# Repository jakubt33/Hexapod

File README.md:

Hexapod
=======

0b00 - Start communication in manual mode
0b01 - Start communication in auto mode
0b10 - Next bite
0b11 - End of message

Manual:
0b00|x x x x x x
0b10|L L L L L L 
0b10|L T T T T T
0b11|S S S S S P

Auto:
0b01|C C C C C c
0b11|c S S S S P

x - wchich leg is to be activated (1-6)
L - lift position
T - turn position
S - speed
P - power on(1)/power off(0)
c - command
C - Curve

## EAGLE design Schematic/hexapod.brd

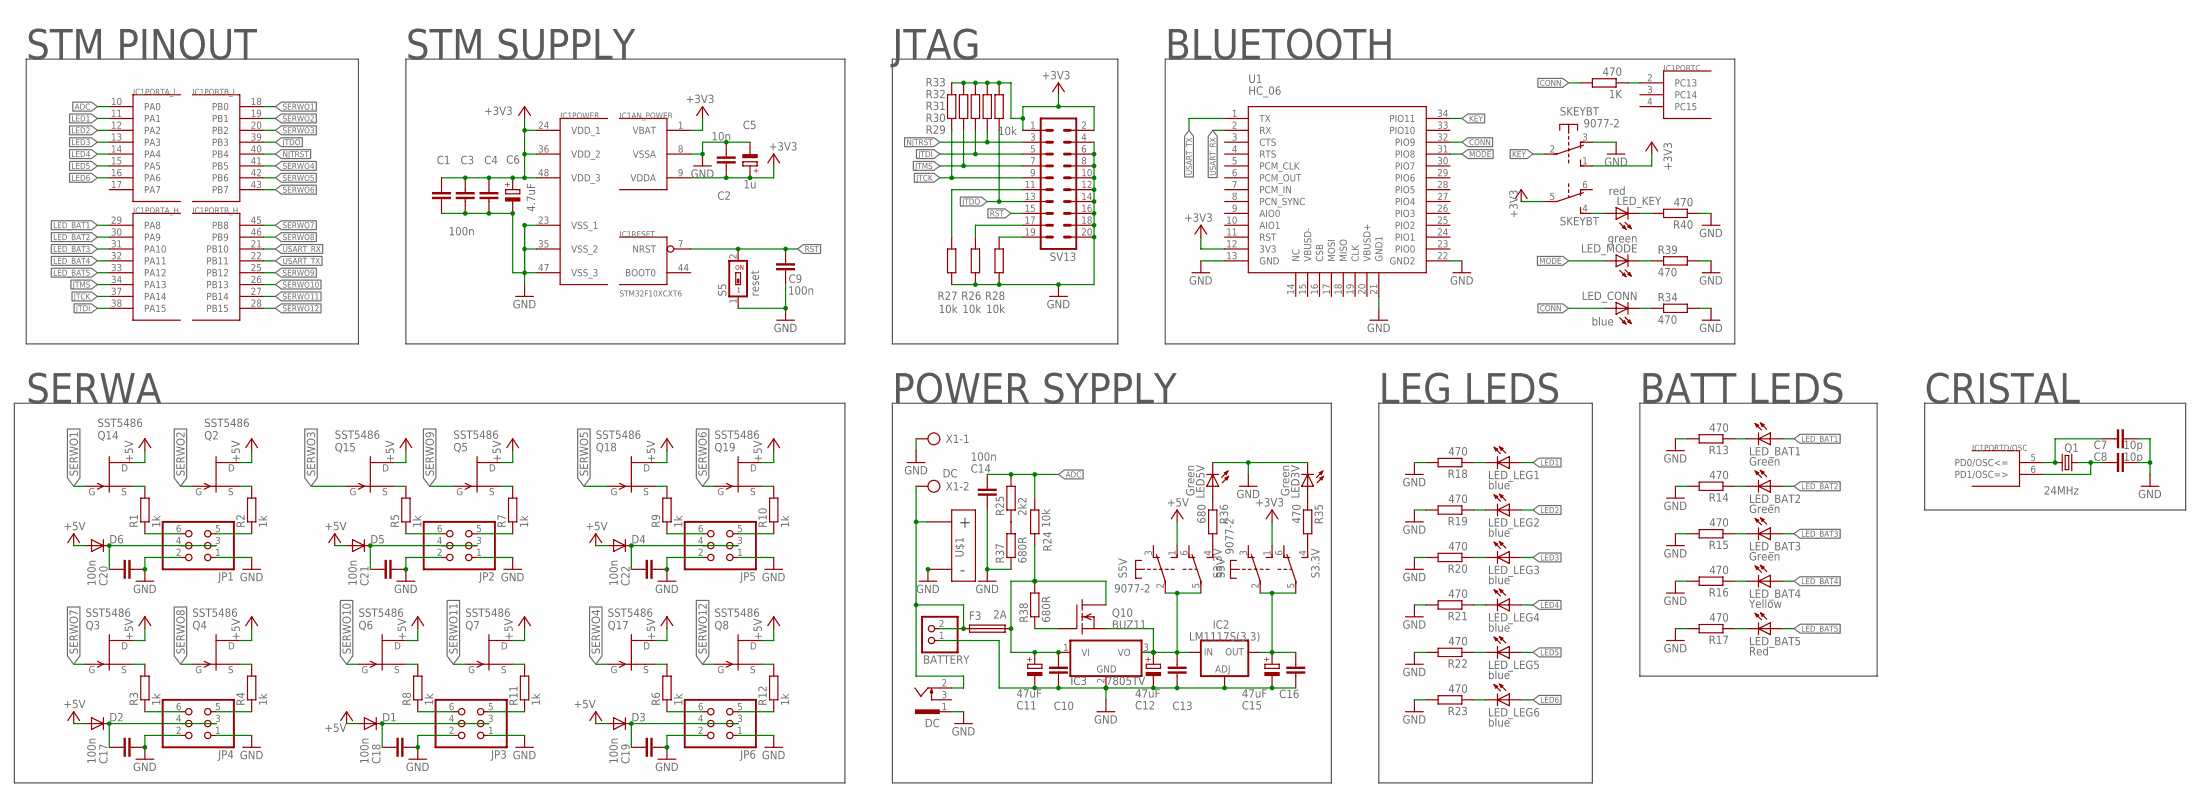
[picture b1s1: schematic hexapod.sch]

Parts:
1K: 470; M0805
BATTERY: PINHD-1X2; 1X02
C1, C3, C4, C9, C10, C13, C14, C16, C17, C18, C19, C20, C21, C22: 100n; C0805K
C2: 10n; C0805K
C5: 1u; E2,5-5
C6: 4.7uF; E2,5-5
C7, C8: 10p; C0805K
C11, C12, C15: 47uF; E2,5-5
D1, D2, D3, D4, D5, D6: DIODE-DO-214AC; DO-214AC
DC: 733980-62
F3: 2A; SH22,5
IC1: STM32F10XCXT6; TQFP48
IC2: LM1117S(3.3); SOT223
IC3: 7805TV; TO220V
JP1, JP2, JP3, JP4, JP5, JP6: PINHD-2X3; 2X03
LED3V, LED5V: Green; CHIP-LED0805
LED_BAT1, LED_BAT2, LED_BAT3: Green; CHIP-LED0805
LED_BAT4: Yellow; CHIP-LED0805
LED_BAT5: Red; CHIP-LED0805
LED_CONN: blue; CHIP-LED0805
LED_KEY: red; CHIP-LED0805
LED_LEG1, LED_LEG2, LED_LEG3, LED_LEG4, LED_LEG5, LED_LEG6: blue; CHIP-LED0805
LED_MODE: green; CHIP-LED0805
Q1: 24MHz; SM49
Q2, Q3, Q4, Q5, Q6, Q7, Q8, Q14, Q15, Q17, Q18, Q19: SST5486; SOT23
Q10: BUZ11; TO220
R1, R2, R3, R4, R5, R6, R7, R8, R9, R10, R11, R12: 1k; M0805
R13, R14, R15, R16, R17, R18, R19, R20, R21, R22, R23, R34, R35, R39, R40: 470; M0805
R24, R26, R27, R28, R29, R30, R31, R32, R33: 10k; M0805
R25: 2k2; M0805
R36: 680; M0805
R37, R38: 680R; M0805
S3.3V, S5V: 9077-2
S5: reset; SMS-001
SKEYBT: 9077-2
SV13: ML20
U1: HC_06; BLUETOOTH_SMD
U$1: DEANS.MALE; DEANSM
X1: DC; AK500/2

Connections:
+3V3: C1.1, C2.1, C3.1, C4.1, C5.+, C6.+, IC1.1 (VBAT), IC1.9 (VDDA), IC1.24 (VDD_1), IC1.36 (VDD_2), IC1.48 (VDD_3), R29.2, R30.2, R31.2, R32.2, R33.2, S3.3V.1 (S), SKEYBT.1 (S), SKEYBT.5, SV13.1, SV13.2, U1.12 (3V3)
+5V: D1.A, D2.A, D3.A, D4.A, D5.A, D6.A, Q2.1 (D), Q3.1 (D), Q4.1 (D), Q5.1 (D), Q6.1 (D), Q7.1 (D), Q8.1 (D), Q14.1 (D), Q15.1 (D), Q17.1 (D), Q18.1 (D), Q19.1 (D), S5V.1 (S)
ADC: C14.1, IC1.10 (PA0), R24.1, R25.2
CONN: 1K.2, LED_CONN.A, U1.32 (PIO9)
GND: BATTERY.1, C1.2, C2.2, C3.2, C4.2, C5.-, C6.-, C7.2, C8.2, C9.1, C10.2, C11.-, C12.-, C13.2, C14.2, C15.-, C16.2, C17.2, C18.2, C19.2, C20.2, C21.2, C22.2, DC.1, IC1.8 (VSSA), IC1.23 (VSS_1), IC1.35 (VSS_2), IC1.47 (VSS_3), IC2.1 (ADJ), IC3.2 (GND), JP1.1, JP1.2, JP2.1, JP2.2, JP3.1, JP3.2, JP4.1, JP4.2, JP5.1, JP5.2, JP6.1, JP6.2, LED3V.C, LED5V.C, R13.2, R14.2, R15.2, R16.2, R17.2, R18.2, R19.2, R20.2, R21.2, R22.2, R23.2, R26.1, R27.1, R28.1, R34.2, R37.1, R39.2, R40.1, S5.1, SKEYBT.3 (O), SV13.4, SV13.6, SV13.8, SV13.10, SV13.12, SV13.14, SV13.16, SV13.18, SV13.20, U1.13 (GND), U1.21 (GND1), U1.22 (GND2), U$1.P$NEG, X1.1
JTCK: IC1.37 (PA14), R29.1, SV13.9
JTDI: IC1.38 (PA15), R31.1, SV13.5
JTDO: IC1.39 (PB3), R33.1, SV13.13
JTMS: IC1.34 (PA13), R30.1, SV13.7
KEY: SKEYBT.2, U1.34 (PIO11)
LED1: IC1.11 (PA1), LED_LEG1.A
LED2: IC1.12 (PA2), LED_LEG2.A
LED3: IC1.13 (PA3), LED_LEG3.A
LED4: IC1.14 (PA4), LED_LEG4.A
LED5: IC1.15 (PA5), LED_LEG5.A
LED6: IC1.16 (PA6), LED_LEG6.A
LED_BAT1: IC1.29 (PA8), LED_BAT1.A
LED_BAT2: IC1.30 (PA9), LED_BAT2.A
LED_BAT3: IC1.31 (PA10), LED_BAT3.A
LED_BAT4: IC1.32 (PA11), LED_BAT4.A
LED_BAT5: IC1.33 (PA12), LED_BAT5.A
MODE: LED_MODE.A, U1.31 (PIO8)
unnamed: C7.1, IC1.5 (PD0/OSC<=), Q1.2
unnamed: C8.1, IC1.6 (PD1/OSC=>), Q1.1
unnamed: 1K.1, IC1.2 (PC13)
unnamed: Q14.2 (S), R1.2
unnamed: JP5.5, R10.1
unnamed: Q2.2 (S), R2.2
unnamed: JP3.5, R11.1
unnamed: JP5.6, R9.1
unnamed: JP3.6, R8.1
unnamed: R25.1, R37.2
unnamed: JP6.5, R12.1
unnamed: Q15.2 (S), R5.2
unnamed: JP2.5, R7.1
unnamed: Q18.2 (S), R9.2
unnamed: JP2.6, R5.1
unnamed: JP6.6, R6.1
unnamed: JP1.6, R1.1
unnamed: JP4.6, R3.1
unnamed: JP4.5, R4.1
unnamed: Q19.2 (S), R10.2
unnamed: JP1.5, R2.1
unnamed: R36.2, S5V.4 (S)
unnamed: C10.1, C11.+, F3.2, IC3.1 (VI), Q10.2 (D), R24.2, R38.2
unnamed: Q10.1 (G), R38.1
unnamed: LED_MODE.C, R39.1
unnamed: LED_KEY.A, SKEYBT.4 (S)
unnamed: LED_KEY.C, R40.2
unnamed: LED_BAT1.C, R13.1
unnamed: LED_LEG1.C, R18.1
unnamed: LED_BAT2.C, R14.1
unnamed: LED_LEG2.C, R19.1
unnamed: LED_BAT3.C, R15.1
unnamed: LED_LEG3.C, R20.1
unnamed: LED_BAT4.C, R16.1
unnamed: LED_LEG4.C, R21.1
unnamed: LED_BAT5.C, R17.1
unnamed: LED_LEG5.C, R22.1
unnamed: LED_LEG6.C, R23.1
unnamed: C18.1, D1.C, JP3.3, JP3.4
unnamed: LED_CONN.C, R34.1
unnamed: C15.+, C16.1, IC2.4 (OUT), S3.3V.2, S3.3V.5
unnamed: C12.+, C13.1, IC2.3 (IN), IC3.3 (VO), Q10.3 (S), S5V.2, S5V.5
unnamed: Q17.2 (S), R6.2
unnamed: R27.2, SV13.11
unnamed: Q3.2 (S), R3.2
unnamed: R35.2, S3.3V.4 (S)
unnamed: R26.2, SV13.17
unnamed: R28.2, SV13.19
unnamed: LED3V.A, R35.1
unnamed: C17.1, D2.C, JP4.3, JP4.4
unnamed: LED5V.A, R36.1
unnamed: BATTERY.2, DC.2, F3.1, U$1.P$POS, X1.2
unnamed: Q4.2 (S), R4.2
unnamed: Q5.2 (S), R7.2
unnamed: Q6.2 (S), R8.2
unnamed: Q7.2 (S), R11.2
unnamed: Q8.2 (S), R12.2
unnamed: C19.1, D3.C, JP6.3, JP6.4
unnamed: C22.1, D4.C, JP5.3, JP5.4
unnamed: C21.1, D5.C, JP2.3, JP2.4
unnamed: C20.1, D6.C, JP1.3, JP1.4
NJTRST: IC1.40 (PB4), R32.1, SV13.3
RST: C9.2, IC1.7 (NRST), S5.2, SV13.15
SERWO1: IC1.18 (PB0), Q14.3 (G)
SERWO2: IC1.19 (PB1), Q2.3 (G)
SERWO3: IC1.20 (PB2), Q15.3 (G)
SERWO4: IC1.41 (PB5), Q17.3 (G)
SERWO5: IC1.42 (PB6), Q18.3 (G)
SERWO6: IC1.43 (PB7), Q19.3 (G)
SERWO7: IC1.45 (PB8), Q3.3 (G)
SERWO8: IC1.46 (PB9), Q4.3 (G)
SERWO9: IC1.25 (PB12), Q5.3 (G)
SERWO10: IC1.26 (PB13), Q6.3 (G)
SERWO11: IC1.27 (PB14), Q7.3 (G)
SERWO12: IC1.28 (PB15), Q8.3 (G)
USART_RX: IC1.21 (PB10), U1.2 (RX)
USART_TX: IC1.22 (PB11), U1.1 (TX)

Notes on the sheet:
SERWA
BATT LEDS
LEG LEDS
POWER SYPPLY
JTAG
STM SUPPLY
CRISTAL
STM PINOUT
BLUETOOTH

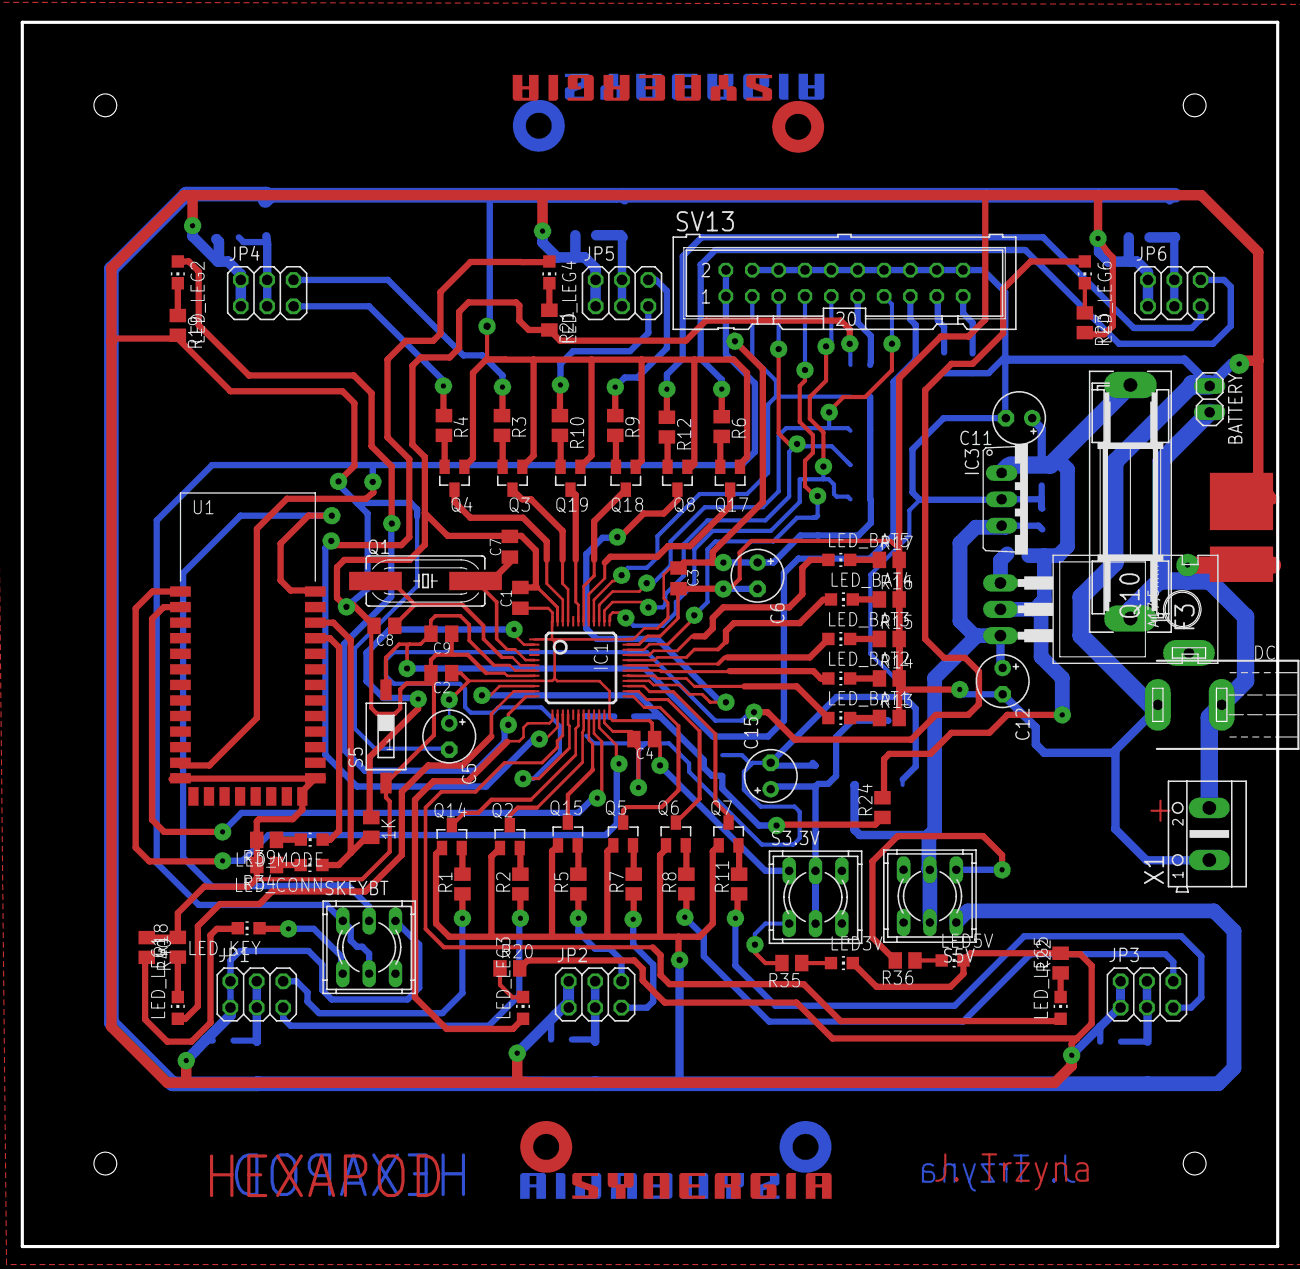
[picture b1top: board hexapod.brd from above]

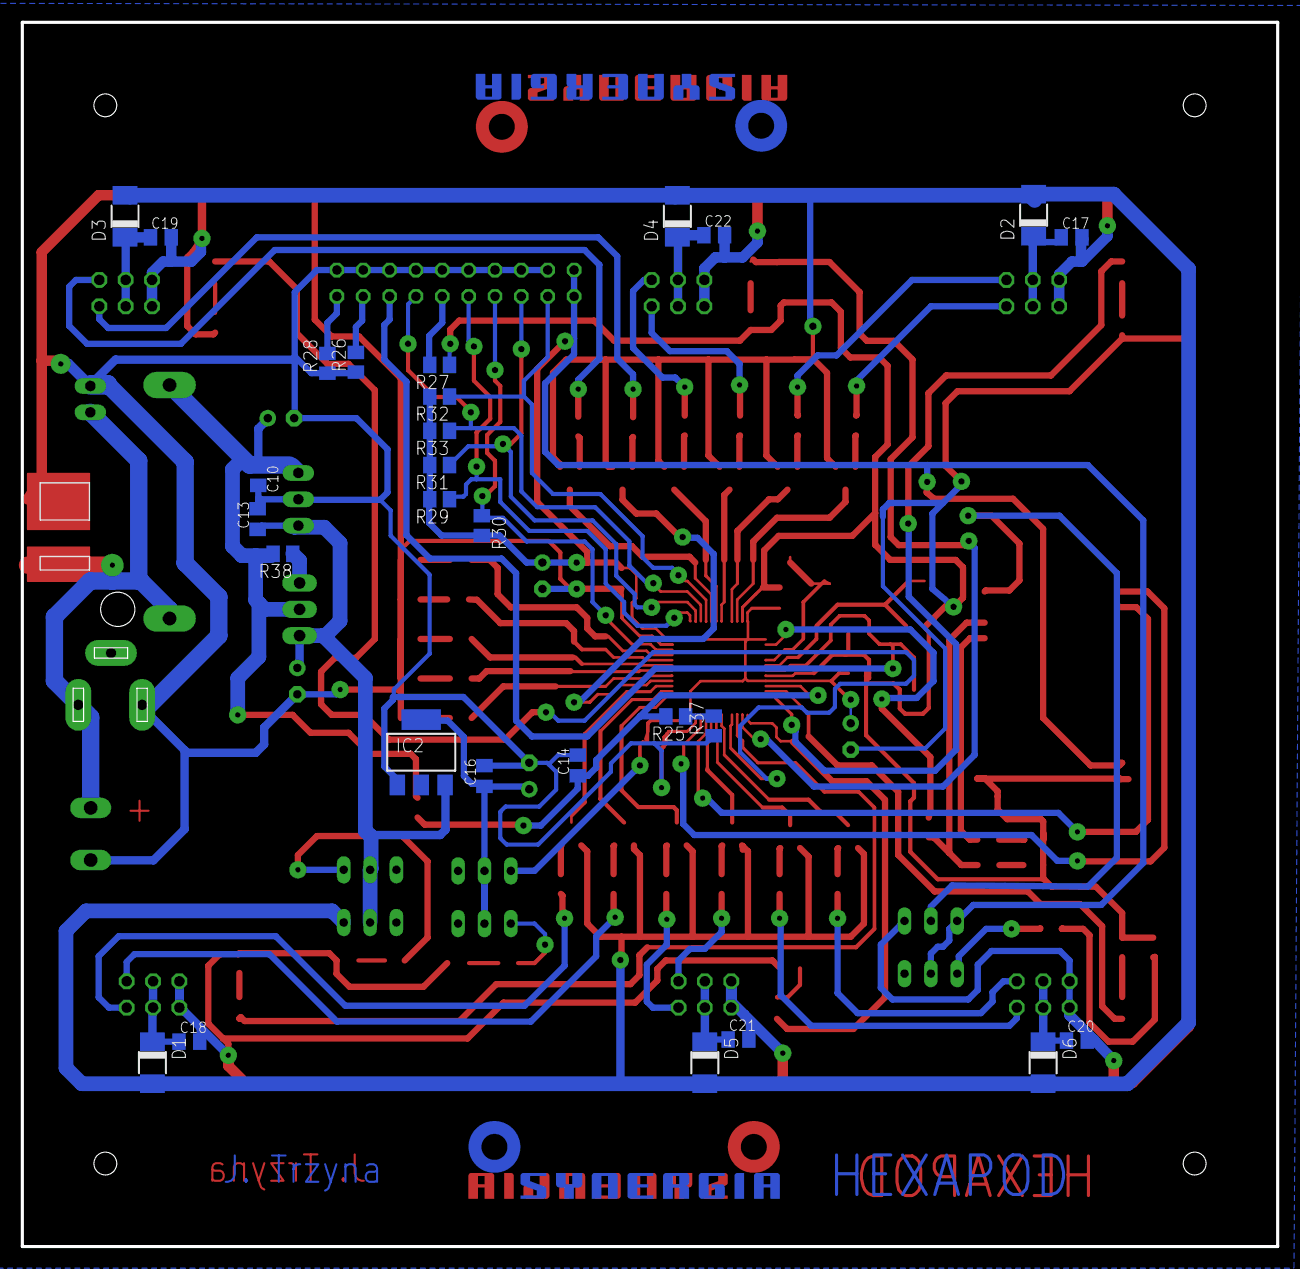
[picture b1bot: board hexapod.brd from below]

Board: 2 copper layers, 121.0 x 118.0 mm, 123 parts (30 on the bottom side), 99 nets.

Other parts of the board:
U$2, U$3, U$4, U$5: SYNERGIA_30MM

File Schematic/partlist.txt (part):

Partlist

Exported from hexapod.brd at 2014-07-22 17:38:38

EAGLE Version 6.4.0 Copyright (c) 1988-2013 CadSoft

Assembly variant: 

Part     Value          Package       Library             Position (inch)       Orientation

BATTERY                 1X02          pinhead             (5.87 1.42)           R90
C1       100n           C0805K        rcl                 (2.52 2.8)            R90
C2       10n            C0805K        rcl                 (2.22 2.53)           R180
C3       100n           C0805K        rcl                 (3.12 2.89)           R270
C4       100n           C0805K        rcl                 (2.99 2.28)           R180
C5       1u             E2,5-5        rcl                 (2.25 2.29)           R270
C6       4.7uF          E2,5-5        rcl                 (3.42 2.9)            R270
C7       10p            C0805K        rcl                 (2.48 3.01)           R90
C8       10p            C0805K        rcl                 (1.98 2.71)           R180
C9       100n           C0805K        rcl                 (2.2 2.71)            R0
C10      100n           C0805K        rcl                 (4.05 2.87)           MR90
C11      47uF           E2,5-5        rcl                 (4.25 2.78)           R270
C12      47uF           E2,5-5        rcl                 (4.25 2.52)           R270
C13      100n           C0805K        rcl                 (4 2.54)              MR270
C14      100n           C0805K        rcl                 (4.16 2.02)           R90
C15      47uF           E2,5-5        rcl                 (3.47 2.14)           R90
C16      100n           C0805K        rcl                 (3.64 2.14)           MR90
DC                      733980-62     con-conrad          (5.79 2.28)           R90
F3       2A             SH22,5        fuse                (4.57 2.39)           R90
IC1      STM32F10XCXT6  TQFP48        stm32               (2.75 2.55)           R270
IC2      LM1117S(3.3)   SOT223        v-reg               (3.92 2.23)           MR0
IC4      LM1117S(5)     SOT223        v-reg               (3.78 2.7)            MR180
LED3V    Green          CHIP-LED0805  led                 (3.74 1.43)           R270
LED5V    Green          CHIP-LED0805  led                 (4.16 1.44)           R270
LED_BAT1 Green          CHIP-LED0805  led                 (3.71 2.36)           R270
LED_BAT2 Green          CHIP-LED0805  led                 (3.71 2.51)           R270
LED_BAT3 Green          CHIP-LED0805  led                 (3.71 2.66)           R270
LED_BAT4 Yellow         CHIP-LED0805  led                 (3.71 2.81)           R270
LED_BAT5 Red            CHIP-LED0805  led                 (3.71 2.96)           R270
LED_CONN blue           CHIP-LED0805  led                 (1.72 1.89)           R90
LED_LEG1 blue           CHIP-LED0805  led                 (1.22 1.28)           R0
LED_LEG2 blue           CHIP-LED0805  led                 (1.22 4.07)           R180
LED_LEG3 blue           CHIP-LED0805  led                 (2.53 1.27)           R0
LED_LEG4 blue           CHIP-LED0805  led                 (2.63 4.05)           R180
LED_LEG5 blue           CHIP-LED0805  led                 (4.8 1.24)            R0
LED_LEG6 blue           CHIP-LED0805  led                 (4.55 4.05)           R180
POT_ADC  5k             3223G         pot                 (3.79 2.07)           R90
Q1       24MHz          SM49          crystal             (2.16 2.88)           R0
Q2       SST5486        SOT23         transistor-fet      (2.48 1.91)           R0
Q3       SST5486        SOT23         transistor-fet      (2.49 3.27)           R180
Q4       SST5486        SOT23         transistor-fet      (2.27 3.27)           R180
Q5       SST5486        SOT23         transistor-fet      (2.91 1.92)           R0
Q6       SST5486        SOT23         transistor-fet      (3.11 1.92)           R0
Q7       SST5486        SOT23         transistor-fet      (3.31 1.92)           R0
Q8       SST5486        SOT23         transistor-fet      (3.32 3.27)           R180
Q14      SST5486        SOT23         transistor-fet      (2.26 1.91)           R0
Q15      SST5486        SOT23         transistor-fet      (2.7 1.92)            R0
Q17      SST5486        SOT23         transistor-fet      (3.12 3.27)           R180
Q18      SST5486        SOT23         transistor-fet      (2.92 3.27)           R180
Q19      SST5486        SOT23         transistor-fet      (2.71 3.27)           R180
R1       1k             M0805         resistor            (2.3 1.71)            R90
R2       1k             M0805         resistor            (2.52 1.71)           R90
R3       1k             M0805         resistor            (2.45 3.47)           R270
R4       1k             M0805         resistor            (2.23 3.47)           R270
R5       1k             M0805         resistor            (2.74 1.71)           R90
R6       1k             M0805         resistor            (3.08 3.47)           R270
R7       1k             M0805         resistor            (2.95 1.71)           R90
R8       1k             M0805         resistor            (3.15 1.71)           R90
R9       1k             M0805         resistor            (2.88 3.47)           R270
R10      1k             M0805         resistor            (2.67 3.47)           R270
R11      1k             M0805         resistor            (3.35 1.71)           R90
R12      1k             M0805         resistor            (3.28 3.48)           R270
R13      470            M0805         resistor            (3.92 2.36)           R0
R14      470            M0805         resistor            (3.92 2.51)           R0
R15      470            M0805         resistor            (3.92 2.66)           R0
R16      470            M0805         resistor            (3.92 2.81)           R0
R17      470            M0805         resistor            (3.92 2.96)           R0
R18      470            M0805         resistor            (1.22 1.49)           R90
R19      470            M0805         resistor            (1.22 3.85)           R270
R20      470            M0805         resistor            (2.49 1.41)           R180
R21      470            M0805         resistor            (2.63 3.87)           R270
R22      470            M0805         resistor            (4.8 1.44)            R90
R23      470            M0805         resistor            (4.55 3.86)           R90
R24      3K9            M0805         resistor            (3.92 2.23)           R0
R25      3k             M0805         resistor            (4.01 2.02)           R270
R26      10k            M0805         resistor            (4.1 3.55)            MR90
R27      10k            M0805         resistor            (3.81 3.71)           MR180
R28      10k            M0805         resistor            (4.2 3.55)            MR90
R29      10k            M0805         resistor            (3.81 3.19)           MR180
R30      10k            M0805         resistor            (3.65 3.09)           MR270
R31      10k            M0805         resistor            (3.81 3.32)           MR180
R32      10k            M0805         resistor            (3.81 3.58)           MR180
R33      10k            M0805         resistor            (3.81 3.45)           MR180
R34      470            M0805         resistor            (1.53 1.89)           R180
R35      470            M0805         resistor            (3.55 1.43)           R180
R36      820            M0805         resistor            (3.98 1.44)           R180
S3.3V    9077-2         9077-2        switch-misc         (3.64 1.68)           R0
S5       reset          SMS-001       smd-special         (2.01 2.29)           R0
S5V      9077-2         9077-2        switch-misc         (4.07 1.68)           R0
SKEYBT   9077-2         9077-2        switch-misc         (1.91 1.45)           R0
SR1                     MA03-1        con-lstb            (1.5 1.4)             R0
SR2                     MA03-1        con-lstb            (1.5 1.26)            R0
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
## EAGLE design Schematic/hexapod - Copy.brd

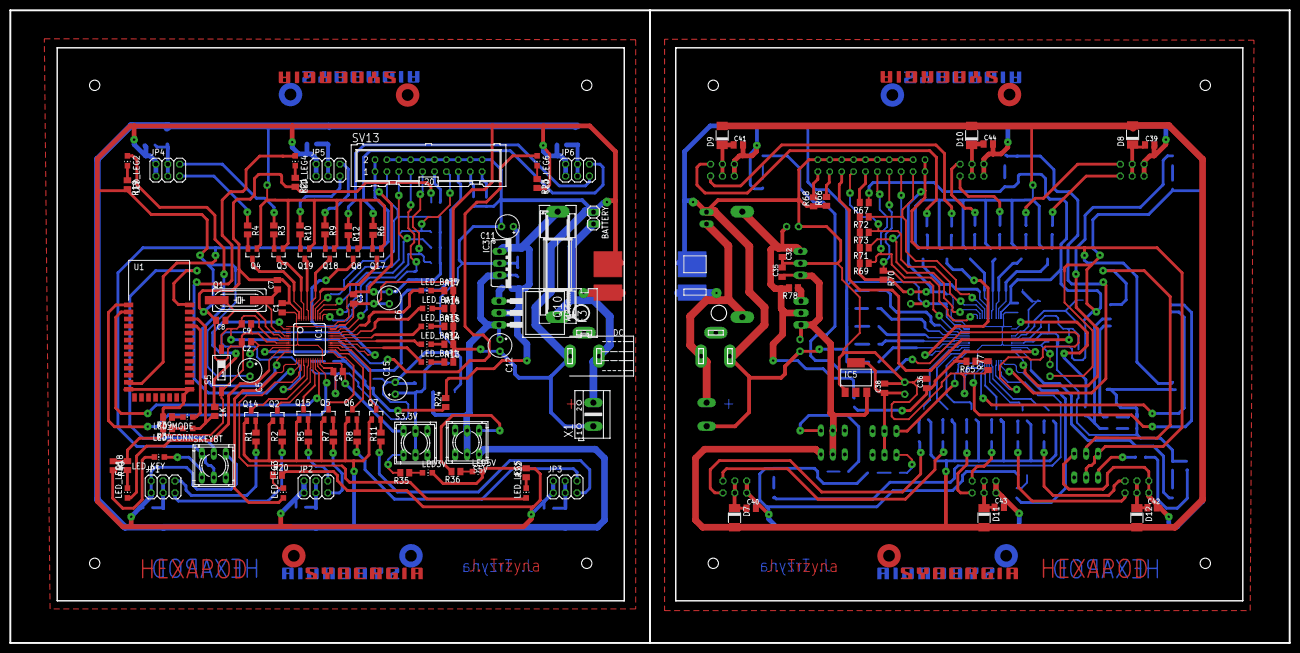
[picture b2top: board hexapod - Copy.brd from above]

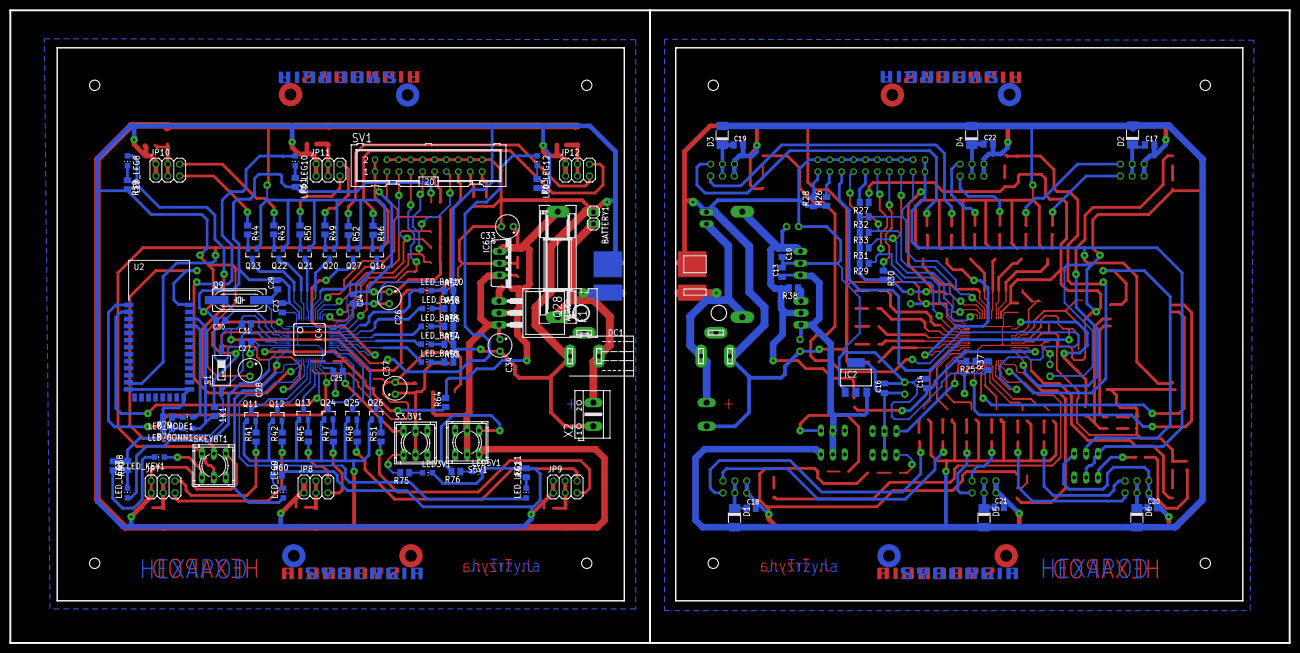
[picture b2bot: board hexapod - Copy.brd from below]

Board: 2 copper layers, 273.0 x 135.0 mm, 246 parts (123 on the bottom side), 198 nets.

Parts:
1K, 1K1: 470; M0805
BATTERY, BATTERY1: 1X02
C1, C3, C4, C9, C10, C13, C14, C16, C17, C18, C19, C20, C21, C22, C23, C24, C25, C31, C32, C35, C36, C38, C39, C40, C41, C42, C43, C44: 100n; C0805K
C2, C27: 10n; C0805K
C5, C28: 1u; E2,5-5
C6, C26: 4.7uF; E2,5-5
C7, C8, C29, C30: 10p; C0805K
C11, C12, C15, C33, C34, C37: 47uF; E2,5-5
D1, D2, D3, D4, D5, D6, D7, D8, D9, D10, D11, D12: DO-214AC
DC, DC1: 733980-62
F1, F3: 2A; SH22,5
IC1, IC4: STM32F10XCXT6; TQFP48
IC2, IC5: LM1117S(3.3); SOT223
IC3, IC6: 7805TV; TO220V
JP1, JP2, JP3, JP4, JP5, JP6, JP7, JP8, JP9, JP10, JP11, JP12: 2X03
LED3V, LED3V1, LED5V, LED5V1: Green; CHIP-LED0805
LED_BAT1, LED_BAT2, LED_BAT3, LED_BAT6, LED_BAT7, LED_BAT8: Green; CHIP-LED0805
LED_BAT4, LED_BAT9: Yellow; CHIP-LED0805
LED_BAT5, LED_BAT10: Red; CHIP-LED0805
LED_CONN, LED_CONN1: blue; CHIP-LED0805
LED_KEY, LED_KEY1: red; CHIP-LED0805
LED_LEG1, LED_LEG2, LED_LEG3, LED_LEG4, LED_LEG5, LED_LEG6, LED_LEG7, LED_LEG8, LED_LEG9, LED_LEG10, LED_LEG11, LED_LEG12: blue; CHIP-LED0805
LED_MODE, LED_MODE1: green; CHIP-LED0805
Q1, Q9: 24MHz; SM49
Q2, Q3, Q4, Q5, Q6, Q7, Q8, Q11, Q12, Q13, Q14, Q15, Q16, Q17, Q18, Q19, Q20, Q21, Q22, Q23, Q24, Q25, Q26, Q27: SST5486; SOT23
Q10, Q28: BUZ11; TO220
R1, R2, R3, R4, R5, R6, R7, R8, R9, R10, R11, R12, R41, R42, R43, R44, R45, R46, R47, R48, R49, R50, R51, R52: 1k; M0805
R13, R14, R15, R16, R17, R18, R19, R20, R21, R22, R23, R34, R35, R39, R40, R53, R54, R55, R56, R57, R58, R59, R60, R61, R62, R63, R74, R75, R79, R80: 470; M0805
R24, R64: 3K9; M0805
R25, R65: 2k2; M0805
R26, R27, R28, R29, R30, R31, R32, R33, R66, R67, R68, R69, R70, R71, R72, R73: 10k; M0805
R36, R76: 680; M0805
R37, R38, R77, R78: 680R; M0805
S1, S5: reset; SMS-001
S3.3V, S3.3V1, S5V, S5V1: 9077-2
SKEYBT, SKEYBT1: 9077-2
SV1, SV13: ML20
U1, U2: HC_06; BLUETOOTH_SMD
U$1, U$6: DEANS.MALE; DEANSM
U$2, U$3, U$4, U$5, U$7, U$8, U$9, U$10: SYNERGIA_30MM
X1, X2: DC; AK500/2

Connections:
+3V1: C23.1, C24.1, C25.1, C26.+, C27.1, C28.+, IC4.1, IC4.9, IC4.24, IC4.36, IC4.48, R69.2, R70.2, R71.2, R72.2, R73.2, S3.3V1.1, SKEYBT1.1, SKEYBT1.5, SV1.1, SV1.2, U2.12
+3V3: C1.1, C2.1, C3.1, C4.1, C5.+, C6.+, IC1.1, IC1.9, IC1.24, IC1.36, IC1.48, R29.2, R30.2, R31.2, R32.2, R33.2, S3.3V.1, SKEYBT.1, SKEYBT.5, SV13.1, SV13.2, U1.12
+5V: D1.A, D2.A, D3.A, D4.A, D5.A, D6.A, Q2.1, Q3.1, Q4.1, Q5.1, Q6.1, Q7.1, Q8.1, Q14.1, Q15.1, Q17.1, Q18.1, Q19.1, S5V.1
+5V1: D7.A, D8.A, D9.A, D10.A, D11.A, D12.A, Q11.1, Q12.1, Q13.1, Q16.1, Q20.1, Q21.1, Q22.1, Q23.1, Q24.1, Q25.1, Q26.1, Q27.1, S5V1.1
ADC: C14.1, IC1.10, R24.1, R25.2
ADC1: C36.1, IC4.10, R64.1, R65.2
CONN: 1K.2, LED_CONN.A, U1.32
CONN1: 1K1.2, LED_CONN1.A, U2.32
GND: BATTERY.1, C1.2, C2.2, C3.2, C4.2, C5.-, C6.-, C7.2, C8.2, C9.1, C10.2, C11.-, C12.-, C13.2, C14.2, C15.-, C16.2, C17.2, C18.2, C19.2, C20.2, C21.2, C22.2, DC.1, IC1.8, IC1.23, IC1.35, IC1.47, IC2.1, IC3.2, JP1.1, JP1.2, JP2.1, JP2.2, JP3.1, JP3.2, JP4.1, JP4.2, JP5.1, JP5.2, JP6.1, JP6.2, LED3V.C, LED5V.C, R13.2, R14.2, R15.2, R16.2, R17.2, R18.2, R19.2, R20.2, R21.2, R22.2, R23.2, R26.1, R27.1, R28.1, R34.2, R37.1, R39.2, R40.1, S5.1, SKEYBT.3, SV13.4, SV13.6, SV13.8, SV13.10, SV13.12, SV13.14, SV13.16, SV13.18, SV13.20, U1.13, U1.21, U1.22, U$1.P$NEG, X1.1
GND1: BATTERY1.1, C23.2, C24.2, C25.2, C26.-, C27.2, C28.-, C29.2, C30.2, C31.1, C32.2, C33.-, C34.-, C35.2, C36.2, C37.-, C38.2, C39.2, C40.2, C41.2, C42.2, C43.2, C44.2, DC1.1, IC4.8, IC4.23, IC4.35, IC4.47, IC5.1, IC6.2, JP7.1, JP7.2, JP8.1, JP8.2, JP9.1, JP9.2, JP10.1, JP10.2, JP11.1, JP11.2, JP12.1, JP12.2, LED3V1.C, LED5V1.C, R53.2, R54.2, R55.2, R56.2, R57.2, R58.2, R59.2, R60.2, R61.2, R62.2, R63.2, R66.1, R67.1, R68.1, R74.2, R77.1, R79.2, R80.1, S1.1, SKEYBT1.3, SV1.4, SV1.6, SV1.8, SV1.10, SV1.12, SV1.14, SV1.16, SV1.18, SV1.20, U2.13, U2.21, U2.22, U$6.P$NEG, X2.1
JTCK: IC1.37, R29.1, SV13.9
JTCK1: IC4.37, R69.1, SV1.9
JTDI: IC1.38, R31.1, SV13.5
JTDI1: IC4.38, R71.1, SV1.5
JTDO: IC1.39, R33.1, SV13.13
JTDO1: IC4.39, R73.1, SV1.13
JTMS: IC1.34, R30.1, SV13.7
JTMS1: IC4.34, R70.1, SV1.7
KEY: SKEYBT.2, U1.34
KEY1: SKEYBT1.2, U2.34
LED1: IC1.11, LED_LEG1.A
LED2: IC1.12, LED_LEG2.A
LED3: IC1.13, LED_LEG3.A
LED4: IC1.14, LED_LEG4.A
LED5: IC1.15, LED_LEG5.A
LED6: IC1.16, LED_LEG6.A
LED7: IC4.11, LED_LEG7.A
LED8: IC4.12, LED_LEG8.A
LED9: IC4.13, LED_LEG9.A
LED10: IC4.14, LED_LEG10.A
LED11: IC4.15, LED_LEG11.A
LED12: IC4.16, LED_LEG12.A
LED_BAT1: IC1.29, LED_BAT1.A
LED_BAT2: IC1.30, LED_BAT2.A
LED_BAT3: IC1.31, LED_BAT3.A
LED_BAT4: IC1.32, LED_BAT4.A
LED_BAT5: IC1.33, LED_BAT5.A
LED_BAT6: IC4.29, LED_BAT6.A
LED_BAT7: IC4.30, LED_BAT7.A
LED_BAT8: IC4.31, LED_BAT8.A
LED_BAT9: IC4.32, LED_BAT9.A
LED_BAT10: IC4.33, LED_BAT10.A
MODE: LED_MODE.A, U1.31
MODE1: LED_MODE1.A, U2.31
unnamed: C7.1, IC1.5, Q1.2
unnamed: C8.1, IC1.6, Q1.1
unnamed: 1K.1, IC1.2
unnamed: Q14.2, R1.2
unnamed: JP5.5, R10.1
unnamed: Q2.2, R2.2
unnamed: JP3.5, R11.1
unnamed: JP5.6, R9.1
unnamed: JP3.6, R8.1
unnamed: R25.1, R37.2
unnamed: JP6.5, R12.1
unnamed: Q15.2, R5.2
unnamed: JP2.5, R7.1
unnamed: Q18.2, R9.2
unnamed: JP2.6, R5.1
unnamed: JP6.6, R6.1
unnamed: JP1.6, R1.1
unnamed: JP4.6, R3.1
unnamed: JP4.5, R4.1
unnamed: Q19.2, R10.2
unnamed: JP1.5, R2.1
unnamed: R36.2, S5V.4
unnamed: C10.1, C11.+, F3.2, IC3.1, Q10.2, R24.2, R38.2
unnamed: Q10.1, R38.1
unnamed: LED_MODE.C, R39.1
unnamed: LED_KEY.A, SKEYBT.4
unnamed: LED_KEY.C, R40.2
unnamed: LED_BAT1.C, R13.1
unnamed: LED_LEG1.C, R18.1
unnamed: LED_BAT2.C, R14.1
unnamed: LED_LEG2.C, R19.1
unnamed: LED_BAT3.C, R15.1
unnamed: LED_LEG3.C, R20.1
unnamed: LED_BAT4.C, R16.1
unnamed: LED_LEG4.C, R21.1
unnamed: LED_BAT5.C, R17.1
unnamed: LED_LEG5.C, R22.1
unnamed: LED_LEG6.C, R23.1
unnamed: C18.1, D1.C, JP3.3, JP3.4
unnamed: LED_CONN.C, R34.1
unnamed: C15.+, C16.1, IC2.4, S3.3V.2, S3.3V.5
unnamed: C12.+, C13.1, IC2.3, IC3.3, Q10.3, S5V.2, S5V.5
unnamed: Q17.2, R6.2
unnamed: R27.2, SV13.11
unnamed: Q3.2, R3.2
unnamed: R35.2, S3.3V.4
unnamed: R26.2, SV13.17
unnamed: R28.2, SV13.19
unnamed: LED3V.A, R35.1
unnamed: C17.1, D2.C, JP4.3, JP4.4
unnamed: LED5V.A, R36.1
unnamed: BATTERY.2, DC.2, F3.1, U$1.P$POS, X1.2
unnamed: Q4.2, R4.2
unnamed: Q5.2, R7.2
unnamed: Q6.2, R8.2
unnamed: Q7.2, R11.2
unnamed: Q8.2, R12.2
unnamed: C19.1, D3.C, JP6.3, JP6.4
unnamed: C22.1, D4.C, JP5.3, JP5.4
unnamed: C21.1, D5.C, JP2.3, JP2.4
unnamed: C20.1, D6.C, JP1.3, JP1.4
unnamed: C29.1, IC4.5, Q9.2
unnamed: C30.1, IC4.6, Q9.1
unnamed: Q11.2, R41.2
unnamed: LED_BAT6.C, R53.1
unnamed: LED_BAT7.C, R54.1
unnamed: LED_BAT8.C, R55.1
unnamed: LED_BAT9.C, R56.1
unnamed: LED_BAT10.C, R57.1
unnamed: LED_LEG7.C, R58.1
unnamed: LED_LEG8.C, R59.1
unnamed: LED_LEG9.C, R60.1
unnamed: LED_LEG10.C, R61.1
unnamed: LED_LEG11.C, R62.1
unnamed: LED_LEG12.C, R63.1
unnamed: R67.2, SV1.11
unnamed: R66.2, SV1.17
unnamed: R68.2, SV1.19
unnamed: LED_CONN1.C, R74.1
unnamed: C37.+, C38.1, IC5.4, S3.3V1.2, S3.3V1.5
unnamed: C34.+, C35.1, IC5.3, IC6.3, Q28.3, S5V1.2, S5V1.5
unnamed: R75.2, S3.3V1.4
unnamed: LED3V1.A, R75.1
unnamed: LED5V1.A, R76.1
unnamed: BATTERY1.2, DC1.2, F1.1, U$6.P$POS, X2.2
unnamed: Q12.2, R42.2
unnamed: Q13.2, R45.2
unnamed: Q16.2, R46.2
unnamed: Q20.2, R49.2
unnamed: Q21.2, R50.2
unnamed: Q22.2, R43.2
unnamed: Q23.2, R44.2
unnamed: Q24.2, R47.2
unnamed: Q25.2, R48.2
unnamed: Q26.2, R51.2
unnamed: Q27.2, R52.2
unnamed: R65.1, R77.2
unnamed: JP7.6, R41.1
unnamed: JP7.5, R42.1
unnamed: JP8.5, R47.1
unnamed: JP8.6, R45.1
unnamed: JP9.5, R51.1
unnamed: JP9.6, R48.1
unnamed: JP10.6, R43.1
unnamed: JP10.5, R44.1
unnamed: JP11.5, R50.1
unnamed: JP11.6, R49.1
unnamed: JP12.5, R52.1
unnamed: JP12.6, R46.1
unnamed: R76.2, S5V1.4
unnamed: C32.1, C33.+, F1.2, IC6.1, Q28.2, R64.2, R78.2
unnamed: Q28.1, R78.1
unnamed: 1K1.1, IC4.2
unnamed: LED_MODE1.C, R79.1
unnamed: LED_KEY1.A, SKEYBT1.4
unnamed: LED_KEY1.C, R80.2
unnamed: C40.1, D7.C, JP9.3, JP9.4
unnamed: C39.1, D8.C, JP10.3, JP10.4
unnamed: C41.1, D9.C, JP12.3, JP12.4
unnamed: C44.1, D10.C, JP11.3, JP11.4
unnamed: C43.1, D11.C, JP8.3, JP8.4
unnamed: C42.1, D12.C, JP7.3, JP7.4
NJTRST: IC1.40, R32.1, SV13.3
NJTRST1: IC4.40, R72.1, SV1.3
RST: C9.2, IC1.7, S5.2, SV13.15
RST1: C31.2, IC4.7, S1.2, SV1.15
SERWO1: IC1.18, Q14.3
SERWO2: IC1.19, Q2.3
SERWO3: IC1.20, Q15.3
SERWO4: IC1.41, Q17.3
SERWO5: IC1.42, Q18.3
SERWO6: IC1.43, Q19.3
SERWO7: IC1.45, Q3.3
SERWO8: IC1.46, Q4.3
SERWO9: IC1.25, Q5.3
SERWO10: IC1.26, Q6.3
SERWO11: IC1.27, Q7.3
SERWO12: IC1.28, Q8.3
SERWO13: IC4.18, Q11.3
SERWO14: IC4.19, Q12.3
SERWO15: IC4.20, Q13.3
SERWO16: IC4.41, Q16.3
SERWO17: IC4.42, Q20.3
SERWO18: IC4.43, Q21.3
SERWO19: IC4.45, Q22.3
SERWO20: IC4.46, Q23.3
SERWO21: IC4.25, Q24.3
SERWO22: IC4.26, Q25.3
SERWO23: IC4.27, Q26.3
SERWO24: IC4.28, Q27.3
USART_RX: IC1.21, U1.2
USART_RX1: IC4.21, U2.2
USART_TX: IC1.22, U1.1
USART_TX1: IC4.22, U2.1

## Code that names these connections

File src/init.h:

/*
 * init.h
 *
 *  Created on: Aug 1, 2014
 *      Author: Jakub Trzyna
 */

#ifndef INIT_H_
#define INIT_H_


volatile unsigned int Batt_4_5_value;
volatile unsigned int Batt_3_5_value;
volatile unsigned int Batt_2_5_value;
volatile unsigned int Batt_1_5_value;
volatile unsigned int Batt_critical_value;


void init_Bluetooth()
{
  //w³¹czenie zegara portu
  RCC_APB2PeriphClockCmd(RCC_APB2Periph_GPIOB, ENABLE);

  //struktura inicjalizacyjna portu
  GPIO_InitTypeDef  GPIO_InitStructure;

  //Pin PB10 - linia nadawcza USART3
  GPIO_InitStructure.GPIO_Pin = GPIO_Pin_10 ;                   //piny które chcemy skonfigurowaæ
  GPIO_InitStructure.GPIO_Mode = GPIO_Mode_AF_PP;               //tryb wyjæ portu - wyjcie push-pull
  GPIO_InitStructure.GPIO_Speed = GPIO_Speed_50MHz;             //szybkoæ wyjcia
  GPIO_Init(GPIOB, &GPIO_InitStructure);

  //Pin PB11 - linia odbiorcza USART3
  GPIO_InitStructure.GPIO_Pin = GPIO_Pin_11 ;                   //piny które chcemy skonfigurowaæ
  GPIO_InitStructure.GPIO_Mode = GPIO_Mode_IPU;               	//tryb wyjæ portu - wyjcie push-pull
  GPIO_InitStructure.GPIO_Speed = GPIO_Speed_50MHz;             //szybkoæ wyjcia
  GPIO_Init(GPIOB, &GPIO_InitStructure);

  //w³¹czenie zegara USARTa
  RCC_APB1PeriphClockCmd(RCC_APB1Periph_USART3, ENABLE);

  USART_InitTypeDef USART_InitStructure;
  USART_InitStructure.USART_BaudRate=9600;                   	 //Prêdkoæ transmisji - 9600BAUD
  USART_InitStructure.USART_Mode= USART_Mode_Tx | USART_Mode_Rx;  //Tryb pracy - w³¹czony odbiornik oraz nadajnik
  USART_InitStructure.USART_Parity=USART_Parity_No;              //Bity parzystosci - brak
  USART_InitStructure.USART_StopBits=USART_StopBits_1;           //Bity stopu - 1
  USART_InitStructure.USART_WordLength=USART_WordLength_8b;      //D³ugosc ramki - 8 bitów
  USART_InitStructure.USART_HardwareFlowControl=USART_HardwareFlowControl_None; //Sprzêtowa kontrola przep³ywu - brak
  USART_Init(USART3,&USART_InitStructure);

    //Uruchomienie USART3
    USART_Cmd(USART3,ENABLE);

  	RCC_APB2PeriphClockCmd(RCC_APB2Periph_GPIOC, ENABLE);
  	//connection established indicator
	GPIO_InitTypeDef GPIO_InitStructur;
	GPIO_StructInit (& GPIO_InitStructur);
	GPIO_InitStructur.GPIO_Pin = CONNECTIONPIN ;
	GPIO_InitStructur.GPIO_Mode = GPIO_Mode_IN_FLOATING;
	GPIO_InitStructur.GPIO_Speed = GPIO_Speed_2MHz;

	GPIO_Init(BTPORT, &GPIO_InitStructur);
}


void init_TIM2()
{
	NVIC_InitTypeDef NVIC_InitStruct;
	TIM_TimeBaseInitTypeDef TIM_InitStruct;

	RCC_APB1PeriphClockCmd(RCC_APB1Periph_TIM2, ENABLE); // w³¹cza zegar dla peryferium TIM2

	TIM_InitStruct.TIM_ClockDivision = TIM_CKD_DIV1; // dzielnik 1
	TIM_InitStruct.TIM_CounterMode = TIM_CounterMode_Up; // licznik w górê
	TIM_InitStruct.TIM_Period = 10*3; // okres licznika 10 us, 2stopnie serwo
	TIM_InitStruct.TIM_Prescaler = 32; // preskaler 56  = 46Hz
	TIM_TimeBaseInit(TIM2, &TIM_InitStruct); // inicjalizuje TIM2

	TIM_ClearFlag( TIM2, TIM_FLAG_Update ); // czyci flagê aktualizacji TIM2
	TIM_ITConfig(TIM2, TIM_IT_Update, ENABLE); // w³¹cza przerwanie aktualizacji TIM2
	TIM_Cmd(TIM2, ENABLE); // w³¹cza timer TIM2

	NVIC_InitStruct.NVIC_IRQChannel = TIM2_IRQn; // wybór linii przerwania
	NVIC_InitStruct.NVIC_IRQChannelCmd = ENABLE; // w³¹czenie linii
	NVIC_InitStruct.NVIC_IRQChannelPreemptionPriority = 0; // priorytet
	NVIC_InitStruct.NVIC_IRQChannelSubPriority = 0; // podgrupa
	NVIC_Init(&NVIC_InitStruct); // inicjalizacja linii przerwania
}

void init_Clock()
{
	ErrorStatus HSEStartUpStatus;
	// Reset ustawien RCC
	RCC_DeInit();
	// Wlacz HSE
	RCC_HSEConfig(RCC_HSE_ON);
	// Czekaj za HSE bedzie gotowy
	HSEStartUpStatus = RCC_WaitForHSEStartUp();

	if(HSEStartUpStatus == SUCCESS)
	{
		FLASH_PrefetchBufferCmd(FLASH_PrefetchBuffer_Enable);
	 	// zwloka dla pamieci Flash
		FLASH_SetLatency(FLASH_Latency_2);

		// HCLK = SYSCLK
		RCC_HCLKConfig(RCC_SYSCLK_Div1);

		  // PCLK2 = HCLK
		  RCC_PCLK2Config(RCC_HCLK_Div1);

		  // PCLK1 = HCLK/2
		  RCC_PCLK1Config(RCC_HCLK_Div2);

		  // PLLCLK = 8Hz *  = 72 MHz
		  RCC_PLLConfig(RCC_PLLSource_PREDIV1, RCC_PLLMul_4);

		  // Wlacz PLL
		  RCC_PLLCmd(ENABLE);
		  // Czekaj az PLL poprawnie sie uruchomi
		  while(RCC_GetFlagStatus(RCC_FLAG_PLLRDY) == RESET);
		  // PLL bedzie zrodlem sygnalu zegarowego


		  RCC_SYSCLKConfig(RCC_SYSCLKSource_PLLCLK);
		  // Czekaj az PLL bedzie sygnalem zegarowym systemu
		  while(RCC_GetSYSCLKSource() != 0x08);
	  }

}

void set_SupplyVoltage(volatile float MaxVoltage)
{
	float ADC_MaxVoltage = MaxVoltage/4.42;
	float ADC_MinVoltage = 1.54; //maxvoltage 8,4

	float ADC_Diffrence = (ADC_MaxVoltage - ADC_MinVoltage)*0.2;
	float x4_5 = ADC_MaxVoltage - ADC_Diffrence;
	float x3_5 = x4_5 - ADC_Diffrence;
	float x2_5 = x3_5 - ADC_Diffrence;
	float x1_5 = x2_5 - ADC_Diffrence;
	float xCritical = x1_5 - ADC_Diffrence;

	Batt_4_5_value = x4_5*256/3.3;
	Batt_3_5_value = x3_5*256/3.3;
	Batt_2_5_value = x2_5*256/3.3;
	Batt_1_5_value = x1_5*256/3.3;
	Batt_critical_value = xCritical*256/3.3;
}

void init_LED()
{
	RCC_APB2PeriphClockCmd(RCC_APB2Periph_GPIOA, ENABLE); //enable clock on leds port

	GPIO_InitTypeDef GPIO_InitStructure;
	GPIO_StructInit (& GPIO_InitStructure);
	GPIO_InitStructure.GPIO_Pin = GPIO_Pin_1 |GPIO_Pin_2 |GPIO_Pin_3 |GPIO_Pin_4 |GPIO_Pin_5 |GPIO_Pin_6| GPIO_Pin_8 |GPIO_Pin_9 |GPIO_Pin_10 |GPIO_Pin_11 |GPIO_Pin_12;
	GPIO_InitStructure.GPIO_Mode = GPIO_Mode_Out_PP;
	GPIO_InitStructure.GPIO_Speed = GPIO_Speed_2MHz;

	GPIO_Init(GPIOA, &GPIO_InitStructure);
}

void init_Servo()
{
	RCC_APB2PeriphClockCmd(RCC_APB2Periph_GPIOB, ENABLE); //enable clock on serwo port

	GPIO_InitTypeDef GPIO_InitStructure;
	GPIO_StructInit (& GPIO_InitStructure);
	GPIO_InitStructure.GPIO_Pin =  SERWO1 | SERWO2 | SERWO3 | SERWO4 | SERWO5 | SERWO6| SERWO7 | SERWO8 | SERWO9 | SERWO10 | SERWO11 | SERWO12;
	GPIO_InitStructure.GPIO_Mode = GPIO_Mode_Out_PP;
	GPIO_InitStructure.GPIO_Speed = GPIO_Speed_2MHz;

	GPIO_Init(GPIOB, &GPIO_InitStructure);
}

void init_ADC()
{
	set_SupplyVoltage(8.3);

	RCC_APB2PeriphClockCmd(RCC_APB2Periph_GPIOA, ENABLE);
	GPIO_InitTypeDef GPIO_InitStructure;
	GPIO_StructInit (& GPIO_InitStructure);
	GPIO_InitStructure.GPIO_Pin = GPIO_Pin_0;
	GPIO_InitStructure.GPIO_Mode = GPIO_Mode_AIN;
	GPIO_Init(GPIOA, &GPIO_InitStructure);

	RCC_APB2PeriphClockCmd(RCC_APB2Periph_ADC1, ENABLE); //conf pin PA0 as intput, ADC mode
	RCC_ADCCLKConfig(RCC_PCLK2_Div2);

	ADC_InitTypeDef ADC_InitStructure;
	ADC_InitStructure.ADC_ContinuousConvMode = ENABLE;
	ADC_InitStructure.ADC_DataAlign = ADC_DataAlign_Right;
	ADC_InitStructure.ADC_ExternalTrigConv = ADC_ExternalTrigConv_None;
	ADC_InitStructure.ADC_Mode = ADC_Mode_Independent;
	ADC_InitStructure.ADC_NbrOfChannel = 1;
	ADC_InitStructure.ADC_ScanConvMode = DISABLE;
	ADC_Init(ADC1, &ADC_InitStructure);

	//conf adc channel
	ADC_RegularChannelConfig(ADC1, ADC_Channel_0, 1, ADC_SampleTime_13Cycles5);

	//start converter
	ADC_Cmd(ADC1, ENABLE);

	//calibration
	ADC_ResetCalibration( ADC1 );
	while(ADC_GetResetCalibrationStatus( ADC1 ));
	ADC_StartCalibration(ADC1);
	while(ADC_GetCalibrationStatus (ADC1) == SET);

	ADC_SoftwareStartConvCmd(ADC1, ENABLE); //start conversion
}

void delay_ms(volatile int LocalCounter)
{
	LocalCounter*=6000;
	while(LocalCounter--);
}

void delay_us(volatile int LocalCounter)
{
	while(LocalCounter--);
}


#endif /* INIT_H_ */
